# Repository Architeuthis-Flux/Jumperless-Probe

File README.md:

# Jumperless Probe
##### a thing to poke your [Jumperless](https://github.com/Architeuthis-Flux/Jumperless) with

You can even wire an OLED to it and have it show you stuff while you're probing (the button is mounted under the display, so you press on the screen itself.

https://github.com/Architeuthis-Flux/Jumperless-Probe/assets/20519442/1eab6d69-ecf2-4003-92da-1a2ce37a83ef

This is a less ghetto version of this:

If you don't feel like opening the schematic, here it is in text:
```
GPIO 18 ---------------------------------,
                                         |
                                          |-  Button
                                         |                  ~2.2KΩ
GPIO 19 ---------------------------------'----------------/\/\/\/\/\----------> Probe

```

And with this thing and a Jumperess, you can do this:

https://github.com/Architeuthis-Flux/Jumperless-Probe/assets/20519442/1b6e1502-1671-44e5-9529-7ad5706b3317

The footprint should basically support any button you can find laying around.

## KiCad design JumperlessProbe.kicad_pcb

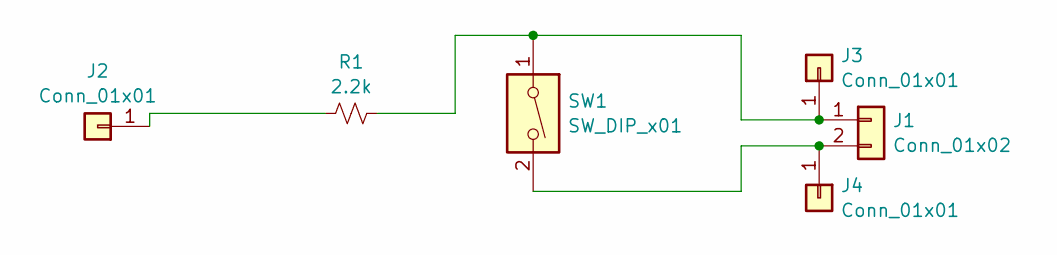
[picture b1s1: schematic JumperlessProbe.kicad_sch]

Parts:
J1: Conn_01x02; Probe_Header
J2: Conn_01x01; ProbeNeedle
J3: Conn_01x01; Pad_Clip_Banana_Probe
J4: Conn_01x01; Pad_Clip_Banana_Button
R1: 2.2k; ResProbe
SW1: SW_DIP_x01; Switch_Universal

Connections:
unnamed: J1.1, J3.1, R1.2, SW1.1
unnamed: J1.2, J4.1, SW1.2
unnamed: J2.1, R1.1

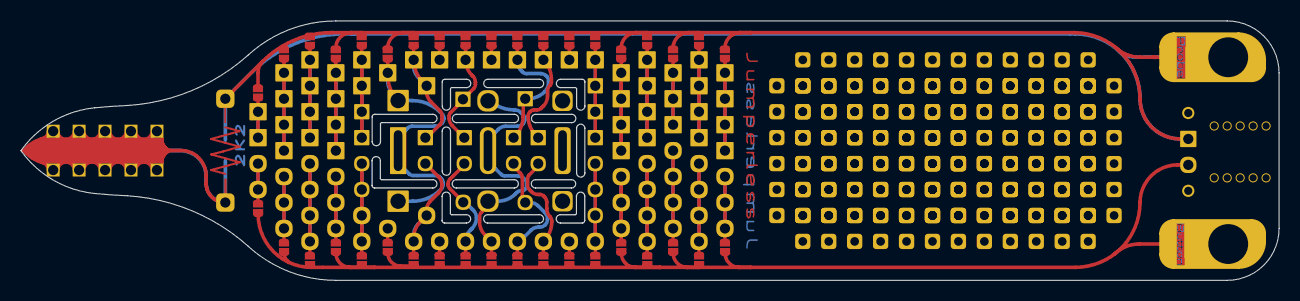
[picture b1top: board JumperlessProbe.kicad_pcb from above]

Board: 2 copper layers, 123.2 x 25.4 mm, 6 parts (0 on the bottom side), 3 nets.

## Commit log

2024-02-24 Added stuff
2024-02-24 removed some nonsense
2024-02-24 debugging kicanvas
2024-02-25 Widened NPTHs
2024-02-25 add a gitignore
2024-02-25 see if gitignore works
